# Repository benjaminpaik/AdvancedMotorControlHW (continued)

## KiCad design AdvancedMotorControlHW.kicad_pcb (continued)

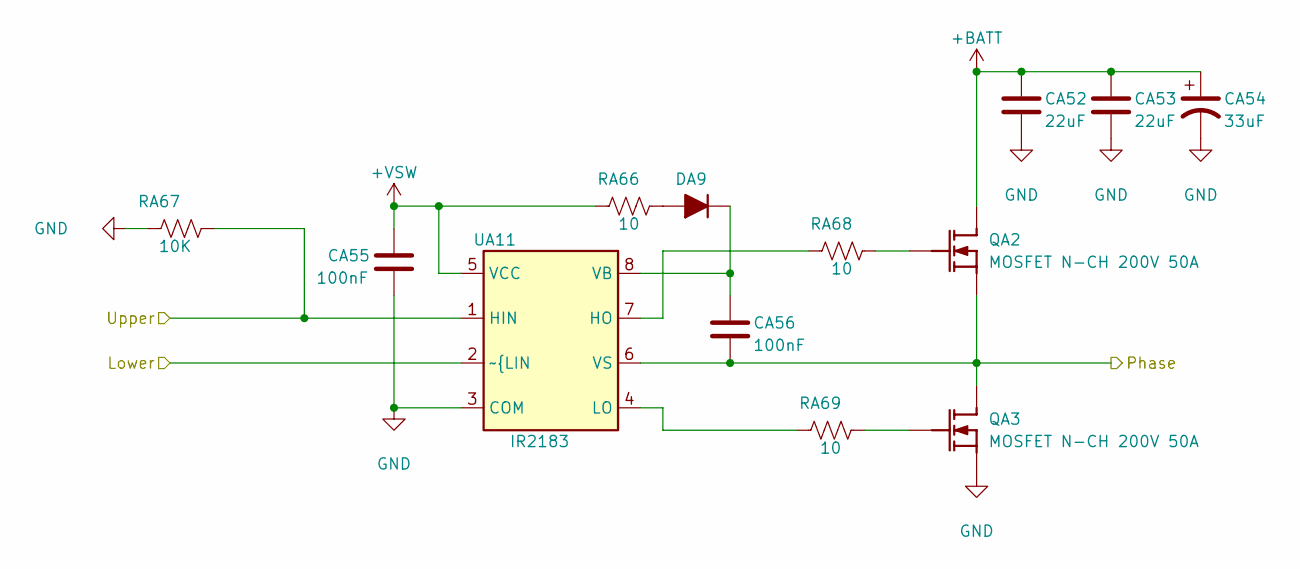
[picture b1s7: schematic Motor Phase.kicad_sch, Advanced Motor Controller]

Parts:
CA52, CA53: 22uF; CAP_CKG57NX7S2A226M500JH; Manufacturer Part Number CKG57NX7S2A226M500JH
CA54: 33uF; CP_Elec_10x10; Manufacturer Part Number EEE-FK2A330P
CA55, CA56: 100nF; C_0603_1608Metric; Manufacturer Part Number 06035G104ZAT2A
DA9: D_SOD-123; Manufacturer Part Number UFM15PL-TP
QA2, QA3: MOSFET N-CH 200V 50A; TO-247AC FaceDown; Manufacturer Part Number IRFP260NPBF
RA66, RA68, RA69: 10; R_0603_1608Metric; Manufacturer Part Number CRCW060310R0JNEAC
RA67: 10K; R_0805_2012Metric; Manufacturer Part Number RR1220P-103-D
UA11: IR2183; SOIC-8_3.9x4.9mm_P1.27mm; Manufacturer Part Number IR2183STRPBF

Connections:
+BATT: CA52.1, CA53.1, CA54.1, QA2.D; also elsewhere on the board
+VSW: CA55.1, RA66.1, UA11.5 (VCC); also elsewhere on the board
/Motor/A/Phase: CA56.2, QA2.S, QA3.D, UA11.6 (VS); also elsewhere on the board
/Motor/Phase A Lower: UA11.2 (~{LIN); also elsewhere on the board
/Motor/Phase A Upper: RA67.2, UA11.1 (HIN); also elsewhere on the board
GND: CA52.2, CA53.2, CA54.2, CA55.2, QA3.S, RA67.1, UA11.3 (COM); also elsewhere on the board
unnamed: DA9.2 (A), RA66.2
unnamed: CA56.1, DA9.1 (K), UA11.8 (VB)
unnamed: QA2.G, RA68.2
unnamed: QA3.G, RA69.2
unnamed: RA68.1, UA11.7 (HO)
unnamed: RA69.1, UA11.4 (LO)

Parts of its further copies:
CB52, CB53: 22uF; CAP_CKG57NX7S2A226M500JH; Manufacturer Part Number CKG57NX7S2A226M500JH
CB54: 33uF; CP_Elec_10x10; Manufacturer Part Number EEE-FK2A330P
CB55, CB56: 100nF; C_0603_1608Metric; Manufacturer Part Number 06035G104ZAT2A
CC52, CC53: 22uF; CAP_CKG57NX7S2A226M500JH; Manufacturer Part Number CKG57NX7S2A226M500JH
CC54: 33uF; CP_Elec_10x10; Manufacturer Part Number EEE-FK2A330P
CC55, CC56: 100nF; C_0603_1608Metric; Manufacturer Part Number 06035G104ZAT2A
DB9: D_SOD-123; Manufacturer Part Number UFM15PL-TP
DC9: D_SOD-123; Manufacturer Part Number UFM15PL-TP
QB2, QB3: MOSFET N-CH 200V 50A; TO-247AC FaceDown; Manufacturer Part Number IRFP260NPBF
QC2, QC3: MOSFET N-CH 200V 50A; TO-247AC FaceDown; Manufacturer Part Number IRFP260NPBF
RB66, RB68, RB69: 10; R_0603_1608Metric; Manufacturer Part Number CRCW060310R0JNEAC
RB67: 10K; R_0805_2012Metric; Manufacturer Part Number RR1220P-103-D
RC66, RC68, RC69: 10; R_0603_1608Metric; Manufacturer Part Number CRCW060310R0JNEAC
RC67: 10K; R_0805_2012Metric; Manufacturer Part Number RR1220P-103-D
UB11: IR2183; SOIC-8_3.9x4.9mm_P1.27mm; Manufacturer Part Number IR2183STRPBF
UC11: IR2183; SOIC-8_3.9x4.9mm_P1.27mm; Manufacturer Part Number IR2183STRPBF

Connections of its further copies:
+BATT: CB52.1, CB53.1, CB54.1, CC52.1, CC53.1, CC54.1, QB2.D, QC2.D; also elsewhere on the board
+VSW: CB55.1, CC55.1, RB66.1, RC66.1, UB11.5 (VCC), UC11.5 (VCC); also elsewhere on the board
/Motor/B/Phase: CB56.2, QB2.S, QB3.D, UB11.6 (VS); also elsewhere on the board
/Motor/Phase B Lower: UB11.2 (~{LIN); also elsewhere on the board
/Motor/Phase B Upper: RB67.2, UB11.1 (HIN); also elsewhere on the board
/Motor/Phase C: CC56.2, QC2.S, QC3.D, UC11.6 (VS); also elsewhere on the board
/Motor/Phase C Lower: UC11.2 (~{LIN); also elsewhere on the board
/Motor/Phase C Upper: RC67.2, UC11.1 (HIN); also elsewhere on the board
GND: CB52.2, CB53.2, CB54.2, CB55.2, CC52.2, CC53.2, CC54.2, CC55.2, QB3.S, QC3.S, RB67.1, RC67.1, UB11.3 (COM), UC11.3 (COM); also elsewhere on the board
unnamed: DB9.2 (A), RB66.2
unnamed: CB56.1, DB9.1 (K), UB11.8 (VB)
unnamed: DC9.2 (A), RC66.2
unnamed: CC56.1, DC9.1 (K), UC11.8 (VB)
unnamed: QB2.G, RB68.2
unnamed: QB3.G, RB69.2
unnamed: QC2.G, RC68.2
unnamed: QC3.G, RC69.2
unnamed: RB68.1, UB11.7 (HO)
unnamed: RB69.1, UB11.4 (LO)
unnamed: RC68.1, UC11.7 (HO)
unnamed: RC69.1, UC11.4 (LO)

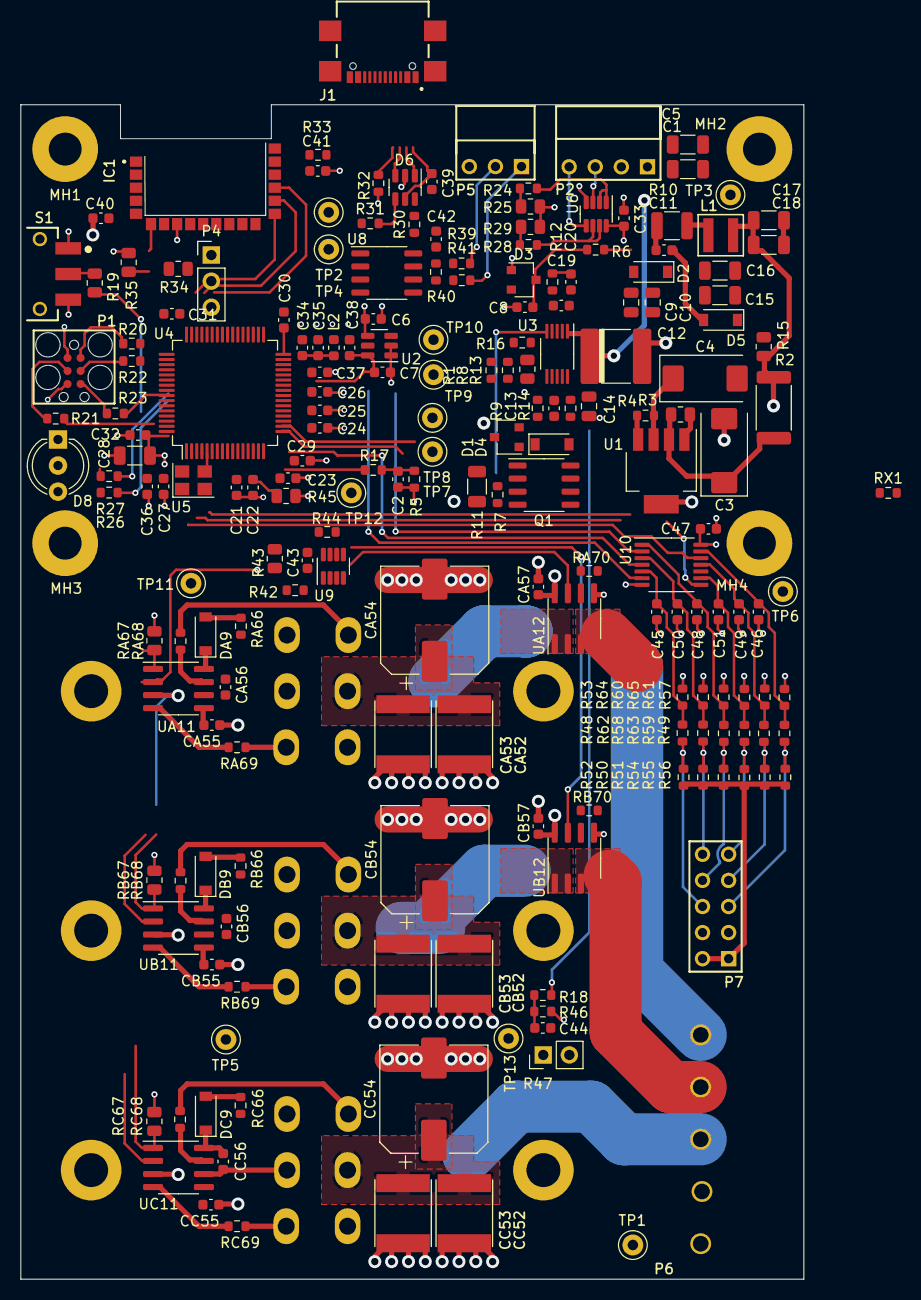
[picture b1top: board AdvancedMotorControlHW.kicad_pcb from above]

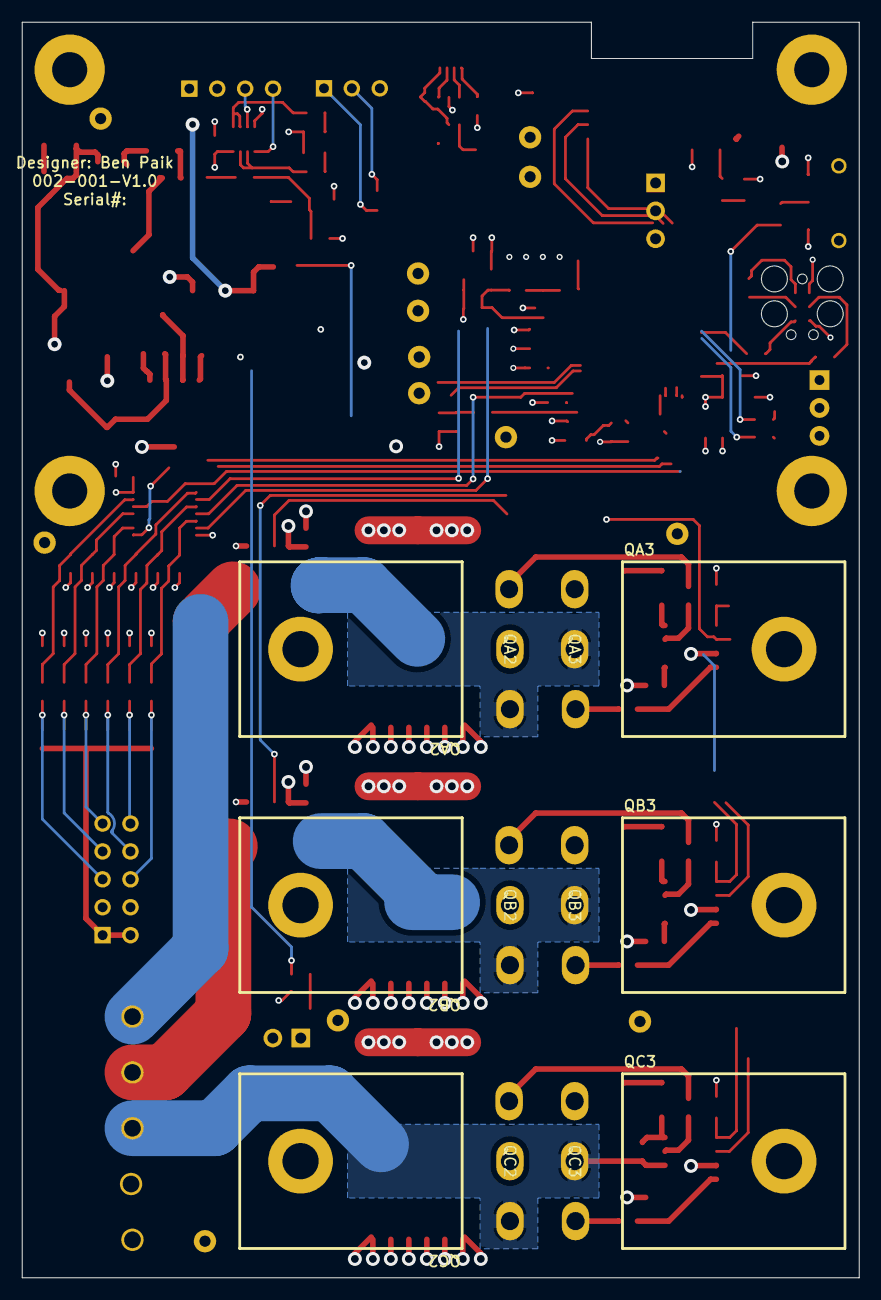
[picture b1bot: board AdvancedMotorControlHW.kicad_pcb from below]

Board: 4 copper layers, 76.2 x 114.3 mm, 204 parts (6 on the bottom side), 134 nets.

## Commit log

2024-06-11 Imported from Altium (power supplies incomplete).
